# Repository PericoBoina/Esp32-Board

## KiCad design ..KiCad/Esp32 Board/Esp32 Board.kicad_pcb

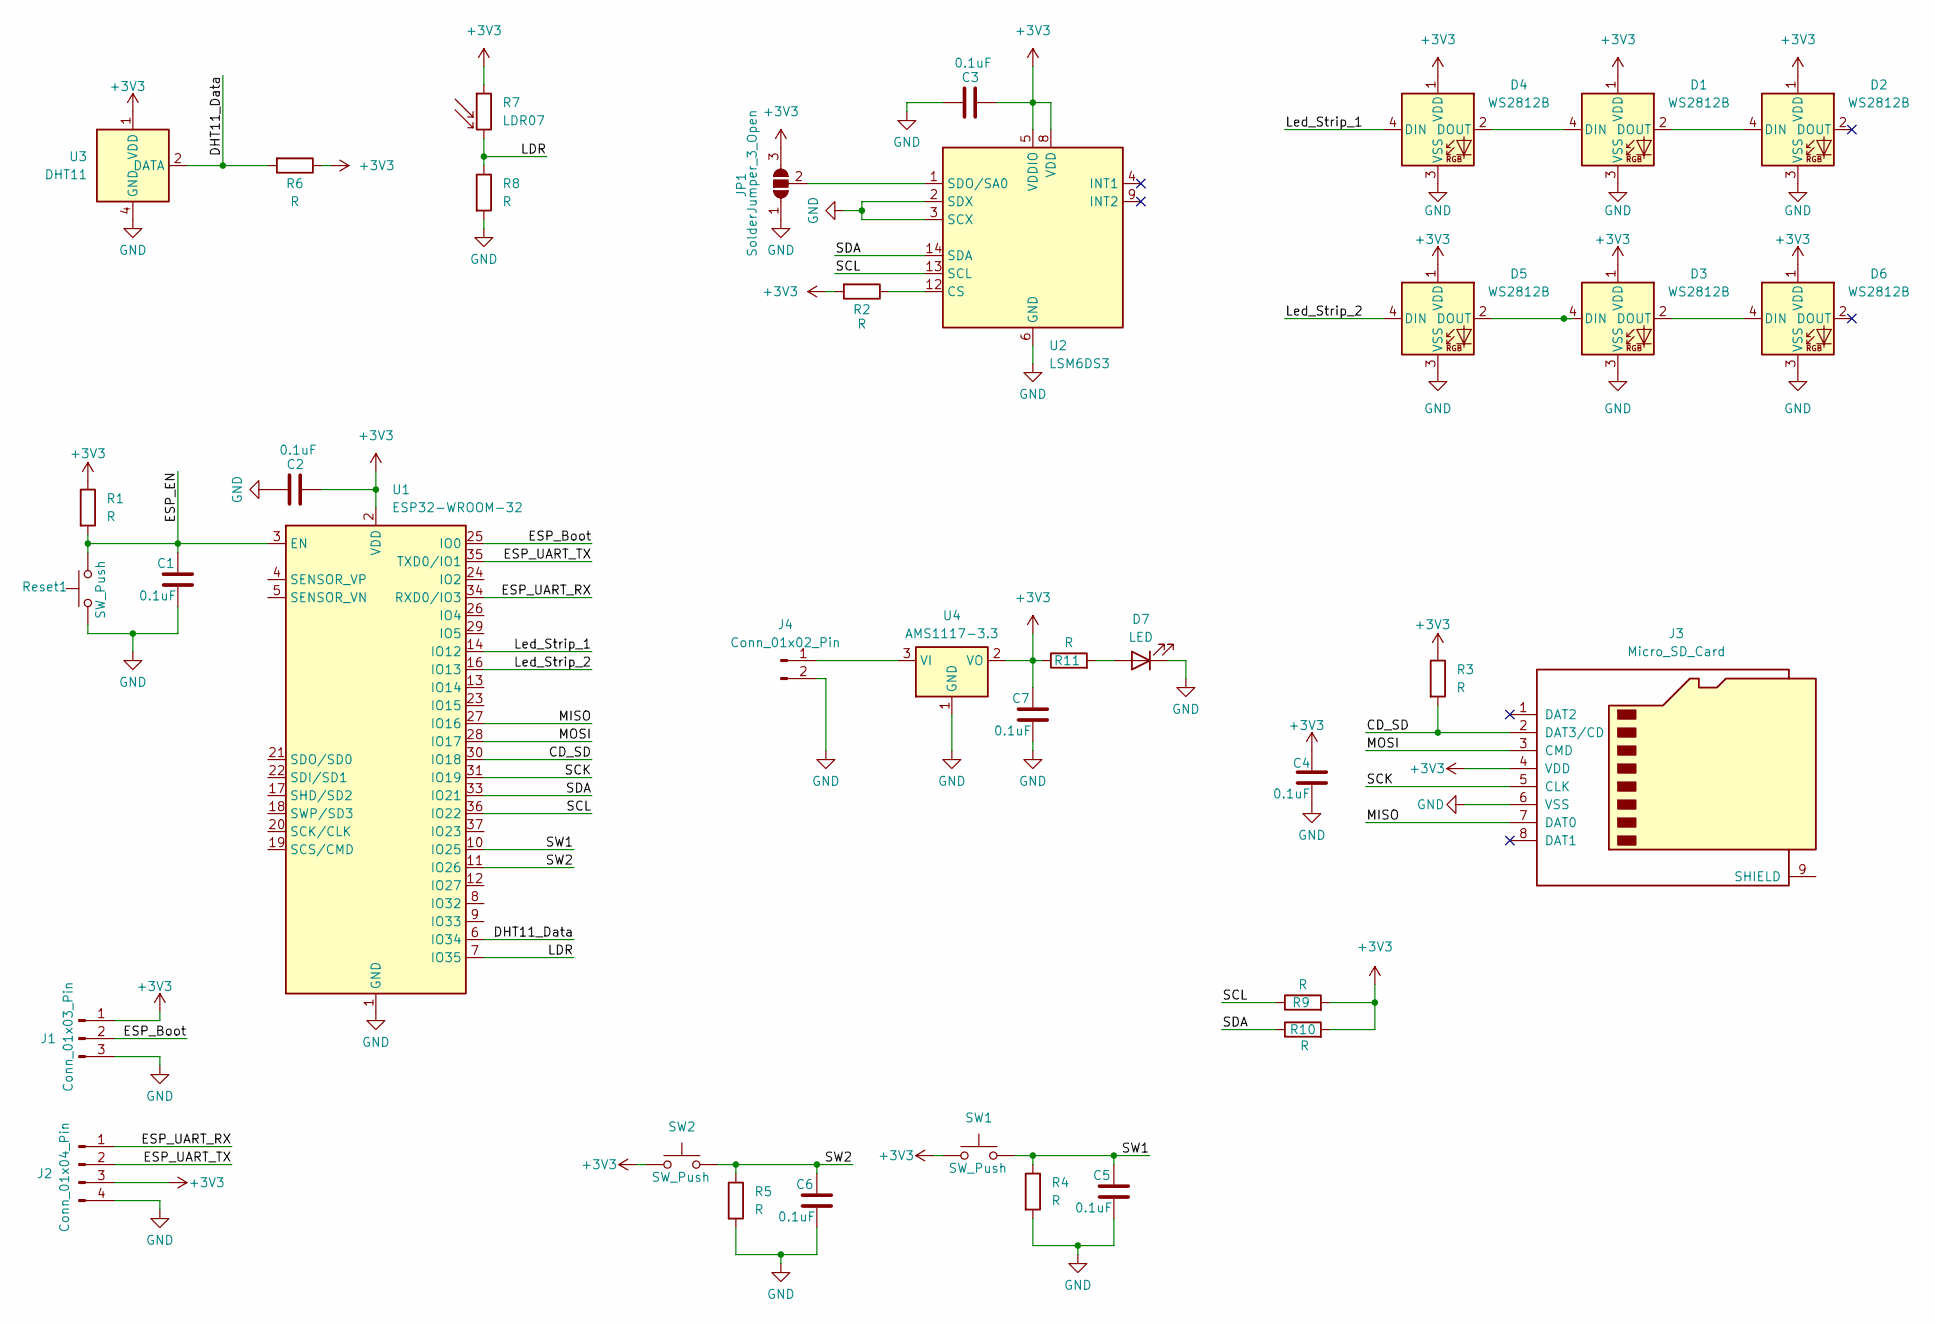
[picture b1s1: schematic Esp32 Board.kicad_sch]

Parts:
C1, C2, C3, C4, C5, C6, C7: 0.1uF; C_0805_2012Metric_Pad1.18x1.45mm_HandSolder
D1, D2, D3, D4, D5, D6: WS2812B; LED_WS2812B_PLCC4_5.0x5.0mm_P3.2mm
D7: LED; LED_0805_2012Metric_Pad1.15x1.40mm_HandSolder
J1: Conn_01x03_Pin; PinHeader_1x03_P2.54mm_Vertical
J2: Conn_01x04_Pin; PinHeader_1x04_P2.54mm_Vertical
J3: Micro_SD_Card; Micro SD socket
J4: Conn_01x02_Pin; JST_XA_B02B-XASK-1_1x02_P2.50mm_Vertical
JP1: SolderJumper_3_Open; SolderJumper-3_P1.3mm_Open_Pad1.0x1.5mm
R1, R2, R3, R4, R5, R6, R8, R9, R10, R11: R; R_0805_2012Metric_Pad1.20x1.40mm_HandSolder
R7: LDR07; R_LDR_5.1x4.3mm_P3.4mm_Vertical
Reset1: SW_Push; SW_Push_1P1T_XKB_TS-1187A
SW1, SW2: SW_Push; SW_Push_1P1T_XKB_TS-1187A
U1: ESP32-WROOM-32
U2: LSM6DS3; LGA-14_3x2.5mm_P0.5mm_LayoutBorder3x4y
U3: DHT11
U4: AMS1117-3.3; SOT-223-3_TabPin2

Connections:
+3V3: C2.1, C3.1, C4.1, C7.1, D1.1 (VDD), D2.1 (VDD), D3.1 (VDD), D4.1 (VDD), D5.1 (VDD), D6.1 (VDD), J1.1, J2.3, J3.4 (VDD), JP1.3 (B), R1.1, R2.2, R3.1, R6.1, R7.1, R9.2, R10.2, R11.1, SW1.1, SW2.1, U1.2 (VDD), U2.5 (VDDIO), U2.8 (VDD), U3.1 (VDD), U4.2 (VO)
/CD_SD: J3.2 (DAT3/CD), R3.2, U1.30 (IO18)
/DHT11_Data: R6.2, U1.6 (IO34), U3.2 (DATA)
/ESP_Boot: J1.2, U1.25 (IO0)
/ESP_EN: C1.1, R1.2, Reset1.2, U1.3 (EN)
/ESP_UART_RX: J2.1, U1.34 (RXD0/IO3)
/ESP_UART_TX: J2.2, U1.35 (TXD0/IO1)
/LDR: R7.2, R8.1, U1.7 (IO35)
/Led_Strip_1: D4.4 (DIN), U1.14 (IO12)
/Led_Strip_2: D5.4 (DIN), U1.16 (IO13)
/MISO: J3.7 (DAT0), U1.27 (IO16)
/MOSI: J3.3 (CMD), U1.28 (IO17)
/SCK: J3.5 (CLK), U1.31 (IO19)
/SCL: R9.1, U1.36 (IO22), U2.13 (SCL)
/SDA: R10.1, U1.33 (IO21), U2.14 (SDA)
/SW1: C5.1, R4.1, SW1.2, U1.10 (IO25)
/SW2: C6.1, R5.1, SW2.2, U1.11 (IO26)
GND: C1.2, C2.2, C3.2, C4.2, C5.2, C6.2, C7.2, D1.3 (VSS), D2.3 (VSS), D3.3 (VSS), D4.3 (VSS), D5.3 (VSS), D6.3 (VSS), D7.1 (K), J1.3, J2.4, J3.6 (VSS), J4.2, JP1.1 (A), R4.2, R5.2, R8.2, Reset1.1, U1.1 (GND), U1.15 (GND), U1.38 (GND), U1.39 (GND), U2.2 (SDX), U2.3 (SCX), U2.6 (GND), U2.7 (GND), U3.4 (GND), U4.1 (GND)
unnamed: D1.4 (DIN), D4.2 (DOUT)
unnamed: D1.2 (DOUT), D2.4 (DIN)
unnamed: D3.4 (DIN), D5.2 (DOUT)
unnamed: D3.2 (DOUT), D6.4 (DIN)
unnamed: D7.2 (A), R11.2
unnamed: J4.1, U4.3 (VI)
unnamed: JP1.2 (C), U2.1 (SDO/SA0)
unnamed: R2.1, U2.12 (CS)

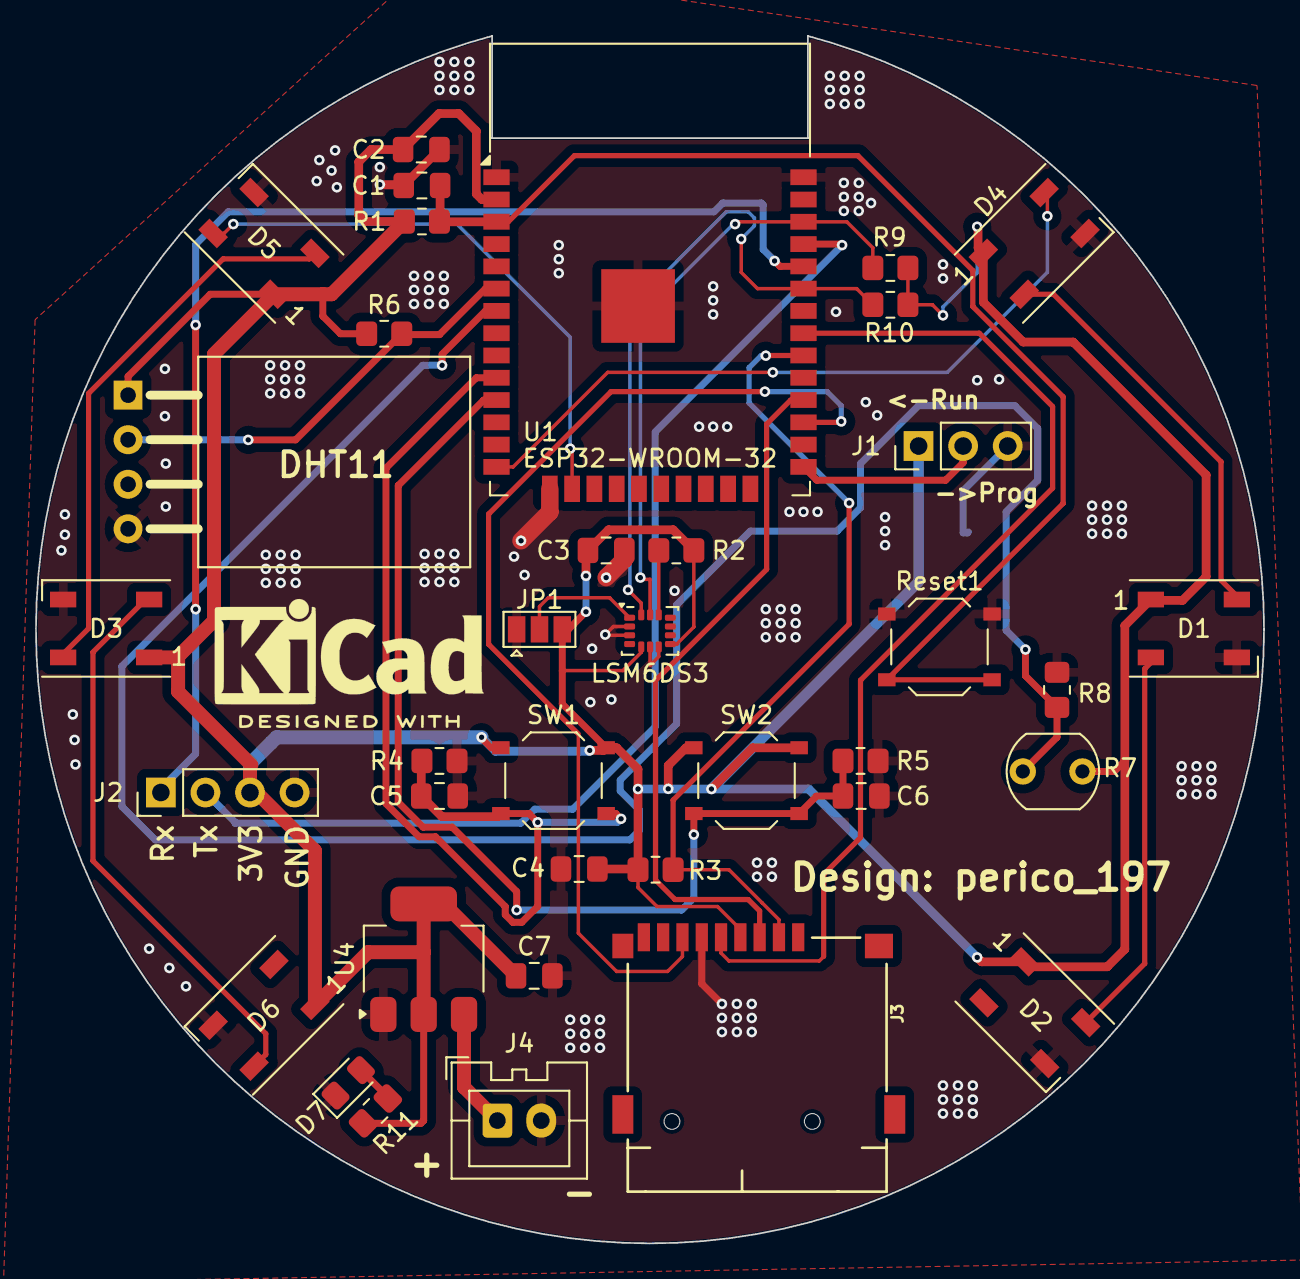
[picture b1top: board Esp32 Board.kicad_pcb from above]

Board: 2 copper layers, 70.0 x 68.8 mm, 37 parts (0 on the bottom side), 26 nets.

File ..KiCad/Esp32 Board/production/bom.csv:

Designator,Footprint,Quantity,Value,LCSC Part #
"C1, C2, C3, C4, C5, C6, C7",0805,7,0.1uF,
"D1, D2, D3, D4, D5, D6",LED_WS2812B_PLCC4_5.0x5.0mm_P3.2mm,6,WS2812B,
D7,0805,1,LED,
J1,PinHeader_1x03_P2.54mm_Vertical,1,Conn_01x03_Pin,
J2,PinHeader_1x04_P2.54mm_Vertical,1,Conn_01x04_Pin,
J3,Micro SD socket,1,Micro_SD_Card,
J4,JST_XA_B02B-XASK-1_1x02_P2.50mm_Vertical,1,Conn_01x02_Pin,
"R1, R10, R11, R2, R3, R4, R5, R6, R8, R9",0805,10,R,
R7,R_LDR_5.1x4.3mm_P3.4mm_Vertical,1,LDR07,
"Reset1, SW1, SW2",SW_Push_1P1T_XKB_TS-1187A,3,SW_Push,
U1,ESP32-WROOM-32,1,ESP32-WROOM-32,
U2,LGA-14_3x2.5mm_P0.5mm_LayoutBorder3x4y,1,LSM6DS3,
U3,DHT11,1,DHT11,
U4,SOT-223-3_TabPin2,1,AMS1117-3.3,
